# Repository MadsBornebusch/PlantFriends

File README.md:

<div align="center">
  
</div>

The code is licensed under the GNU General Public License Version 3.

The PCB is licensed under the Creative Commons Attribution-ShareAlike 4.0 license due to using an [ESP8266 kicad library](https://github.com/jdunmire/kicad-ESP8266) and a particular [soil moisture probe design](https://github.com/acolomitchi/cap-soil-moisture-v2).
_________

This is a plant watering ESP8266.

# Features

* Fully open source (software and hardware)
* Automatic OTA update via Github release - enable/disable using checkbox
* OTA updates via a web interface
* Works with any MQTT server
* Works with Home Assistant discovery
* Set the sleep time, watering delay, water threshold, water time etc via MQTT
* Works with ThingSpeak
* Temperature, pressure and humidity using BME280

# PCB

## Pinout when seen from component side:

Left side from top:

- FTDI_RX
- FTDI_TX
- SDA
- SCL
- GND
- Battery VCC

## Right side from top:

- Battery VCC IN
- GND
- VCC (3.3 V)
- Watering OUT

# Settings

The WiFi, Blynk and MQTT settings can be configured via a web interface:

If you do not want to use Blynk simply leave the `Blynk Auth token` field empty. Similarly the MQTT can be disabled by leaving the `MQTT base topic` empty.

At first boot the module will turn on a hotspot with the SSID: `PlantFriends` and password: `plantsarecool`.

After logging on to the WiFI simply navigate to <http://plantfriends.local> or <http://192.168.4.1> to configure the module.

The device can be put back into hotspot mode by shorting the TX and RX pins and restarting the module.

A new firmware and file system image can be uploaded by navigation to <http://plantfriends.local/update> or <http://192.168.4.1/update>.

## Calibrating the soil moisture sensor
Click "Calibrate Soil moisture sensor". 
Follow the instructions. Some handy tips:
- Don't get the electronics wet, only the sensor part
- When doing the wet calibration, use a half full glass of water (or half empty if you are that tye of person). Half of the sensor should be in water. Otherwise the readings when the sensor is put in soil will be very low. 
- If you need to redo a step in the calibration, just refresh the page.

Images of the wet and dry calibration are shown below:

# [Home Assistant](https://www.home-assistant.io/)

Simply activate [MQTT discovery](https://www.home-assistant.io/docs/mqtt/discovery/) by adding the following to your `configuration.yaml` file:

```yaml
mqtt:
  discovery: true
```

Assuming your plant is named `office` it will now show up as a sensor like so:

TODO: Upate this image!

The name of the plant is taken from the `MQTT base topic` and get be chaned via the [HTTP settings](#Settings) page.

## Advanced Home Assistant configuration

This section will guide you through on how to set the `sleep time`, `watering delay`, `watering threshold` and `watering time` directly via the Home Assitant overview page.

First add the following to your `configuration.yaml` file:

```yaml
input_number:
  office_sleep_time:
    name: Sleep Time
    min: 10
    max: 60
    step: 5
    icon: mdi:sleep
    unit_of_measurement: min
  office_watering_delay:
    name: Watering Delay
    min: 0
    max: 360
    step: 10
    icon: mdi:timer-sand
    unit_of_measurement: min
  office_watering_threshold_pct:
    name: Watering Threshold Pct
    min: 0
    max: 100
    step: 0.1
    icon: mdi:target
    unit_of_measurement: pct
  office_watering_time:
    name: Watering Time
    min: 1
    max: 30
    step: 1
    icon: mdi:water-pump
    unit_of_measurement: s
  office_automatic_ota:
    name: Automatic OTA
    min: 0
    max: 1
    step: 1
    icon: mdi:cellphone-arrow-down
```

This will create four [sliders](https://www.home-assistant.io/integrations/input_number/), one for each parameter. Remember to replace `office` with the `MQTT base topic` you have set via the web interface.

Now add the following to your `automations.yaml` file:

```yaml
- alias: Plant set slider
  trigger:
  - platform: mqtt
    topic: 'plant/+/config'
  action:
  - service: input_number.set_value
    data_template:
      entity_id: input_number.{{ trigger.topic.split('/')[1] }}_sleep_time
      value: "{{ trigger.payload_json.sleep_time | float }}"
  - service: input_number.set_value
    data_template:
      entity_id: input_number.{{ trigger.topic.split('/')[1] }}_watering_delay
      value: "{{ trigger.payload_json.watering_delay | float }}"
  - service: input_number.set_value
    data_template:
      entity_id: input_number.{{ trigger.topic.split('/')[1] }}_watering_threshold_pct
      value: "{{ trigger.payload_json.watering_threshold_pct | float }}"
  - service: input_number.set_value
    data_template:
      entity_id: input_number.{{ trigger.topic.split('/')[1] }}_watering_time
      value: "{{ trigger.payload_json.watering_time | float }}"
  - service: input_number.set_value
    data_template:
      entity_id: input_number.{{ trigger.topic.split('/')[1] }}_automatic_ota
      value: "{{ trigger.payload_json.automatic_ota | float }}"

- alias: Plant slider moved
  trigger:
  - platform: state
    entity_id:
      - input_number.office_sleep_time
      - input_number.office_watering_delay
      - input_number.office_watering_threshold_pct
      - input_number.office_watering_time
      - input_number.office_automatic_ota
  action:
  - service: mqtt.publish
    data_template:
      # The topic should always be the after the dot and before the name of the variable we want to set
      topic: "plant/{{ trigger.entity_id.split('.')[1].split('_')[:-2] | join('_') }}/config"
      retain: true
      payload: >
        {% set topic = trigger.entity_id.split('.')[1].split('_')[:-2] | join('_') %}
        {
          "sleep_time": {{ states('input_number.' + topic + '_sleep_time') | int }},
          "watering_delay": {{ states('input_number.' + topic + '_watering_delay') | int }},
          "watering_threshold": {{ states('input_number.' + topic + '_watering_threshold_pct') | int }},
          "watering_time": {{ states('input_number.' + topic + '_watering_time') | int }},
          "automatic_ota": {{ ((states('input_number.' + topic + '_automatic_ota') | int) > 0) | tojson }}
        }
```

This makes sure that the MQTT config topic is updated when the slider is moved and that the slider is always set to the MQTT config topic when it changes.

Finally you can add the sensors and the inputs slider into on group by adding the following to `groups.yaml`:

```yaml
office_plant:
    name: "Office Plant"
    icon: mdi:sprout
    entities:
    - sensor.office_soil_moisture_pct
    - sensor.office_voltage
    - sensor.office_battery
    - sensor.office_temperature
    - sensor.office_pressure
    - sensor.office_humidity
    - input_number.office_sleep_time
    - input_number.office_watering_delay
    - input_number.office_watering_threshold_pct
    - input_number.office_watering_time
    - input_number.office_automatic_ota
```

Note that the `temperature`, `pressure` and `humidity` sensors are only available if a BME280 is connected.

The plant will now show up in the Home Assistant overview like so:

TODO: Update this image

# Blynk

At the moment Blynk and OTA updates are not compatible. Turn off OTA updates if you are using Blynk.

## Virtual pins

Settings:
- V0: Sleep time
- V1: Watering delay
- V2: Watering threshold in percent
- V3: Watering time
- V4: Automatic OTA

Measurements:
- V16: Soil moisture
- V17: Soil moisture pct
- V18: Voltage
- V19: State of charge (battery pct)
- V20: Temperature
- V21: Pressure
- V22: Humidity
- V23: Gas resistance
- V24: Plant watered

Info:
- V32: sleep num
- V33: Watering delay cycles
- V34: Firmware update couter
- V35: Software version

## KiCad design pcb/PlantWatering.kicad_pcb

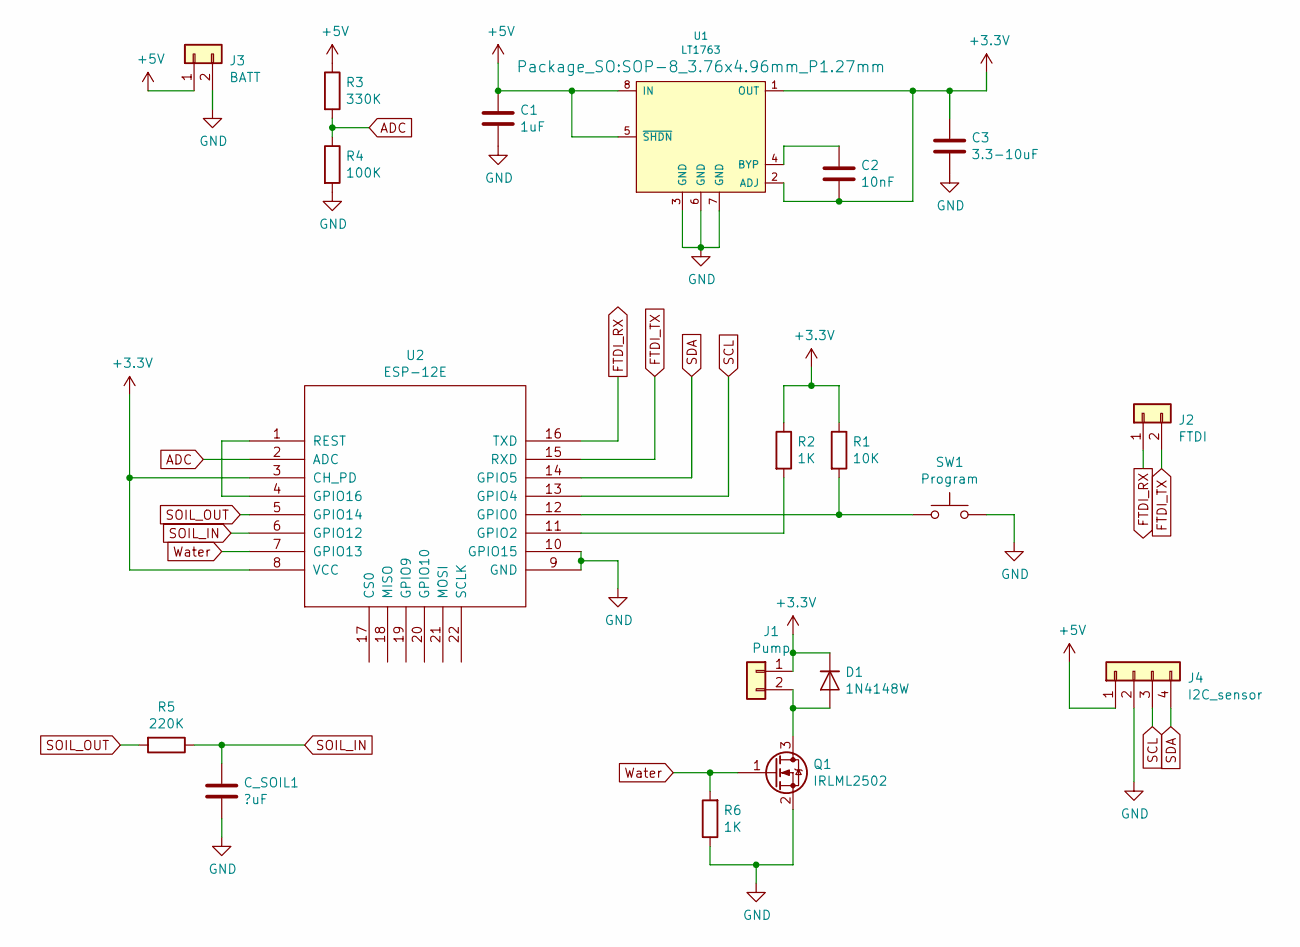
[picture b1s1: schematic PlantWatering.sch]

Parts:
C1: 1uF; C_1206_3216Metric_Pad1.42x1.75mm_HandSolder
C2: 10nF; C_1206_3216Metric_Pad1.42x1.75mm_HandSolder
C3: 3.3-10uF; C_1206_3216Metric_Pad1.42x1.75mm_HandSolder
C_SOIL1: ?uF; C_1206_3216Metric_Pad1.42x1.75mm_HandSolder
D1: 1N4148W; D_SOD-123
J1: Pump; PinHeader_1x02_P2.54mm_Vertical
J2: FTDI; PinHeader_1x02_P2.54mm_Vertical
J3: BATT; JST_PH_B2B-PH-SM4-TB_1x02-1MP_P2.00mm_Vertical
J4: I2C_sensor; PinHeader_1x04_P2.54mm_Vertical
Q1: IRLML2502; SOT-23_Handsoldering
R1: 10K; R_1206_3216Metric_Pad1.42x1.75mm_HandSolder
R2, R6: 1K; R_1206_3216Metric_Pad1.42x1.75mm_HandSolder
R3: 330K; R_1206_3216Metric_Pad1.42x1.75mm_HandSolder
R4: 100K; R_1206_3216Metric_Pad1.42x1.75mm_HandSolder
R5: 220K; R_1206_3216Metric_Pad1.42x1.75mm_HandSolder
SW1: Program; SW_SPST_EVQP7A
U1: LT1763; SOP-8_3.76x4.96mm_P1.27mm
U2: ESP-12E; ESP-12E_SMD

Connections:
+3V3: C2.2, C3.1, D1.1 (K), J1.1, R1.1, R2.1, U1.1 (OUT), U1.2 (ADJ), U2.3 (CH_PD), U2.8 (VCC)
+5V: C1.1, J3.1, J4.1, R3.1, U1.5 (~SHDN), U1.8 (IN)
ADC: R3.2, R4.1, U2.2 (ADC)
FTDI_RX: J2.1, U2.16 (TXD)
FTDI_TX: J2.2, U2.15 (RXD)
GND: C1.2, C3.2, C_SOIL1.2, J3.2, J4.2, Q1.2 (S), R4.2, R6.1, SW1.2, U1.3 (GND), U1.6 (GND), U1.7 (GND), U2.9 (GND), U2.10 (GPIO15)
unnamed: C2.1, U1.4 (BYP)
unnamed: D1.2 (A), J1.2, Q1.3 (D)
unnamed: R1.2, SW1.1, U2.12 (GPIO0)
unnamed: R2.2, U2.11 (GPIO2)
unnamed: U2.1 (REST), U2.4 (GPIO16)
SCL: J4.3, U2.13 (GPIO4)
SDA: J4.4, U2.14 (GPIO5)
SOIL_IN: C_SOIL1.1, R5.1, U2.6 (GPIO12)
SOIL_OUT: R5.2, U2.5 (GPIO14)
Water: Q1.1 (G), R6.2, U2.7 (GPIO13)

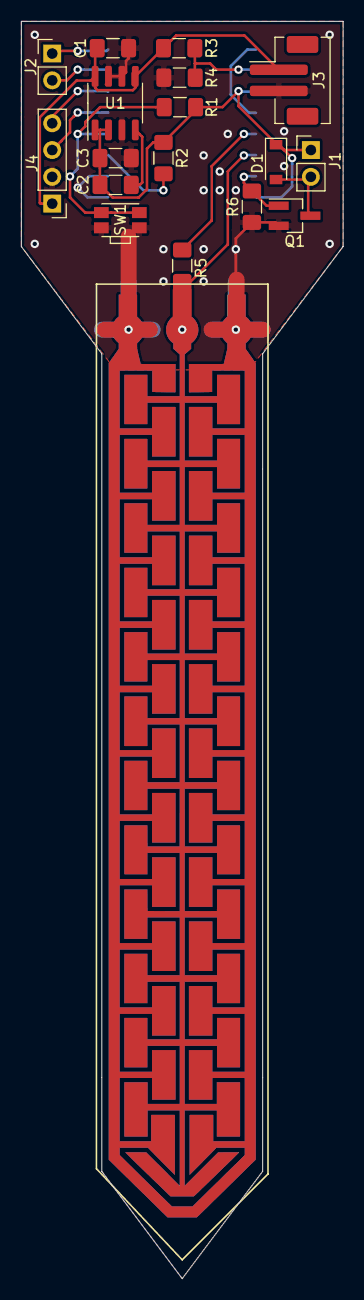
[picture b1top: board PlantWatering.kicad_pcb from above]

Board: 2 copper layers, 30.5 x 119.1 mm, 19 parts (1 on the bottom side), 16 nets.

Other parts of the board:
SFC: sfc*; sqcap-flat

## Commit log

2019-08-05 First commit, first prototype on ESP8266 soil moisture sensing
2019-08-05 Using RTC memory to enable longer deep sleep (or at least several consecutive deep sleeps)
2019-08-05 Bugfix in the long deep sleep, filtering of soil moisture measurement
2019-08-31 Implemented minimum time between watering in order to measure more often without drowning the plant. Also moved LED blink.
2019-10-14 Added README with TODO lists
2019-10-14 Removed todo list, moved data in rtc memory, changed watering threshold
2019-11-16 Set up PlatformIO
2019-11-16 Updated README with PCB pins
2019-11-16 Fix to use interrupts when building with PlatformIO (but it does not build in arduino). Set serial monitor speed
2019-11-16 Added basic commands description to platformio.ini
2019-11-16 Compile and release the project using Github Actions CI
2019-11-16 Added KiCad project with the PCB
2019-11-16 Added LICENSE and checked items of the todo list in README
2019-11-16 Removed delay at boot and flush the serial port instead
2019-11-16 It can now connect and publish the soil moisture and voltage level via MQTT
2019-11-16 Added missing MQTT defines to secret.h
2019-11-17 Store all the configuration values in EEPROM
2019-11-17 It will now create an access point, so the user can set the configuration values at first boot
2019-11-17 Go into AP mode if the TX and RX pins are shorted at boot
2019-11-17 Cleanup the code a little
2019-11-17 Added license for the PCB and details about where the licenses apply in the README
2019-11-20 Style the settings page, so it looks a little nicer
2019-11-20 Fixed bug, as we did not actually wait for the MQTT client to connect
2019-11-20 Only post to ThinkSpeak if the server address is not an empty string
2019-11-20 Publish the MQTT as JSON data and only send via MQTT if the MQTT topic is not an empty string
2019-11-20 Store the MQTT host as a string, as it can be an URL as well
2019-11-20 Use a struct for storing the sleep data in RTC memory
2019-11-21 Added some TODOs
2019-11-21 Cleanup the code
2019-11-21 The user can now set the sleep time, watering delay, watering threshold and watering time via MQTT
2019-11-22 Make sure the JSON payload contains all the keys
2019-11-22 Use a template for the index.html
2019-11-22 Do not hardcode the types when reading the MQTT config
2019-11-22 Build the file system images using the CI
2019-11-22 Just restart if the SPIFFS fails to initialize
2019-11-26 Use a modified version of AsyncElegantOTA for uploading firmware and SPIFFS image via http
2019-11-26 Use mDNS to set a hostname, make sure the IP is always 192.168.4.1 and remove the DNS server
2019-11-26 Renamed stylesheet
2019-11-26 Fixed indentation
2019-11-26 Make sure the EEPROM emulation is always ended
2019-11-26 Support Home Assistant discovery
2019-11-26 Use the EEPROM values on the index page if they have been set
2019-11-26 Allow the user to set the sleep and watering parameters via the web interface as well
2019-11-26 Override the retained config topic, so we do not use the old values after they have been changed via the web interface
2019-11-26 Only interrupt on the rising edge and use a flag to tell when the interrupt has occurred
2019-11-26 Fixed exception, as we can not call function that are not also in IRAM from inside an interrupt
    This seemed to only cause an exception on power on resets
2019-11-26 Make sure the WiFi is turned off before turning on the access point
2019-11-27 The RTC memory read and write did not actually work, as the offset should be given in blocks of 4 bytes
2019-11-27 Include the sleep data in the MQTT state topic
2019-11-27 Set the json_attributes_topic, so device state will automatically show up in Home Assistant
    Also send the software version as part of the state
2019-11-27 Fixed compatibility with Espressif 8266 2.3.0 platform
    This was triggered when the platform was updated from 2.2.3 -> 2.3.0
    See: https://github.com/esp8266/Arduino/commit/a389a995fb12459819e33970ec80695f1eaecc58
2019-11-29 Blink the LED when the board is updating
2019-11-29 Save more strings in flash
    Also just send the HTTP post request to the root
2019-11-29 Do not override the existing file system image on OTA
    See: https://github.com/esp8266/Arduino/pull/6505
2019-11-29 Updated guide on how to use the device with Home Assistant
2019-11-29 Move license up under the header and added TODO on where to add pictures
2019-11-29 Only override the config topic if the value where actaully changed, fixed HTTP POST form response HTTP code and only reset the "override_retained_config_topic" variable if the message was actually pu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
2019-11-29 Cleanup TODO and added ThingSpeak heading
2019-12-30 Changed screenshot of settings
2019-12-30 Calculate the MD5 sum of the compiled binaries, as this will be used to OTA
2020-01-02 Added code for automatically updating the firmware and SPIFFS image via OTA
2020-01-03 Renamed all references to "Plant Watering ESP8266" to "Plant Friends"
2020-01-03 Added new version of the settings image
2020-01-03 Renamed the .ino file to the new name
2020-01-03 Allow for only some of the config varaibles to be provided via MQTT, so the user does not have to set all of them if they have not changed
2020-01-03 Added Let's Encrypt CA certificate, so update works via HTTPS
2020-01-05 Move the TODOs out of the README
2020-01-20 Handle when the soil moisture timer overflow correctly
    This was caused due to the fact that it was a signed integer aka int
2020-01-20 Added the logo to the README
2020-01-20 Release version 1.0.1
2020-04-11 Added support for the BME280 temperature, pressure and humidity sensor
2020-04-18 Round the reported values and changed the temperature icon
2020-04-18 Updated Home Assistant card screenshot
2020-04-18 Release version 1.1.0
2020-05-01 Added calibration routine for soil moisture sensor
2020-05-01 Added png images of schematic and PCB
2020-05-01 Created html pages for the calibration steps
2020-05-01 Fixed bug in soil moisture measurement that would cause absurdly high readings. Added sorting and median, changed calibration html responses to use sites
2020-05-01 Tried to add watering threshold in pct, didn't seem to work
2020-05-01 Forgot to increase size of JSON document after adding a new configuration parameter
2020-05-01 Using watering threshold in percent to decide if we are watering
2020-05-02 Removed old watering threshold
2020-05-02 Calculating state of charge of battery
2020-05-02 Removed watering threshold from setup page
2020-05-03 Fixes from code review
2020-05-03 added images
2020-05-03 Updated README.md with calibration guide and images
2020-05-03 Fixed some more in the readme
2020-05-03 Updated settings screenshot
2020-05-03 Updated some comments in the readme
2020-05-03 Updated settings iage again
2020-05-03 Always watering at full throttle
2020-05-03 Fixed review comments
2020-05-03 Fixed review comments I had missed before
2020-05-12 Added support for BME680
2020-05-12 Using median of soil measurements instead of mean
2020-05-12 Sending gas sensor over mqtt
2020-05-13 Changed sleep interval calculation so interval can be set with 1 min precision as opposed to 10 min before
2020-05-18 Increased json buffer
2020-05-20 Added enclosure files
2020-06-29 Not sending VOC gas resistance if the value is 0
2020-06-29 Changed how battery SOC is calculated to use piecewise linear interpolation
2020-06-29 Added mqtt message to show when the plant is watered. The message is the watering time when the plant is watered and 0 otherwise
2020-06-29 Changed icon for plant watered sensor
2020-07-05 Fixed some compile warnings in PlatformIO
2020-07-05 Fixed bugs in calculations of state of charge and soil moisture percentage. Also changed when gas sensor value is sent
2020-07-05 Added partial support for Blynk
2020-07-05 Swapped Thinkspeak key with Blynk key in build file
2020-07-07 ESP only restarts during OTA and when in hotspot mode
2020-09-07 Fixed some floats
2020-12-28 Updated Readme with Blynk OTA issue
